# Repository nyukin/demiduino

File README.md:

Demiduino
=========

Hardware
--------

Demiduino is an open source
hardware circuit board designed to
introduce people to electronics
prototyping and the Arduino
platform.

The PCB design is inspired by an
Arduino, but divided in both
dimensions by 2.4. This makes it
smaller than an SD card and less
than 1 square inch in total.

There are only about a dozen
components, and they are all
through-hole mounted so that the
circuit can be assembled by
somebody who has had no previous
experience with soldering.

The microcontroller is a socketed
ATtiny85, so that replacing it or
leaving it in another circuit is
practical.

Power is provided by a USB mini
port or lithium battery cell with a
standard connector, and is
regulated by a 3 volt regulator.
This enables compatibiltiy with
many sensors and modules and low
power consumption.

Because the circuit focuses on low
BOM cost and part count to reach a
wider audience (read: I can give it
away to my friends without going
broke), there are some compromises
made that are a little dubious. A
proper engineer who went to college
has made a device that this one is
heavily based on, and it's called
the Trinket by Adafruit. It's
probably more reliable, but
features entirely SMD components.

Software
--------

The Trinket bootloader has been
recompiled from source with my own
USB VID/PID pair. This is to
appease the USB police and so I
must ask that you don't use my USB
pair for derivative work. I'll
happily detail how I accomplished
this and probably should write a
tutorial at least for my own
reference, because all this took me
a couple days to figure out.

To make the IDE work, I also have
recompiled avrdude 6, changing the
USBispTiny VID/PID pair to my own
as well. Then I drop the new
avrdude bin into ./Contents/Resources/Java/hardware/tools/avr/bin.
This is the same path for the
avrdude.conf file. Basically I
forked the Adafruit Trinket Arduino
IDE I had on my system and now it
won't work with a Trinket, so I
have more than one copy of the IDE
installed.

I also modified the boards.txt,
programmers.txt, and theme files.
The first two files were just to
cut out the uneccessary stuff, and
the theme file was to make a dark
colorscheme for the IDE that pays
homage to OSHPark's awesome purple
boards. Compiling avrdude was done
on Ubuntu... narwhal? I forget, but
I like narwhals so lets go with
that. And the IDE runs both on that
linux machine and on OS X 10.9.
Also the libraries I'm using in the
IDE need to be cleaned up to only
be what's compatible with
Demiduino.

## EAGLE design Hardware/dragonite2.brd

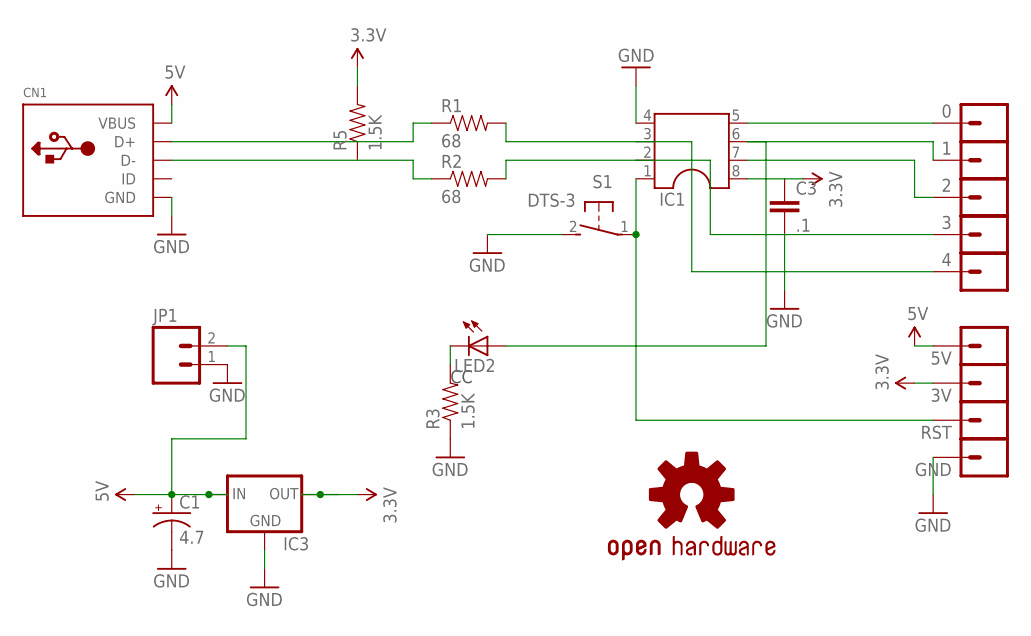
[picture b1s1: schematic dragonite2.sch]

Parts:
0, 1, 2, 3, 3V, 4, 5V: M01SMDNS; 1X01NS
C1: 4.7; E2-4
C3: .1; CAP-PTH-SMALLEZ
CN1: USBMOLEX; USB-MINIB-THM-MOLEX
GND: M01SMDNS; 1X01NS
IC1: DIL8; DIL08
IC3: V_REG_78XXTO-92; TO-92
JP1: M02JST-PTH-2; JST-2-PTH
LED2: LED3MM
R1, R2: 68; 1/6W-RES
R3, R5: 1.5K; 1/6W-RES
RST: M01SMDNS; 1X01NS
S1: DTS-3
U$4: OSHW-LOGOS; OSHW-LOGO-S

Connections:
3.3V: 3V.1, C3.1, IC1.8, IC3.3 (OUT), R5.2
5V: 5V.1, C1.+, CN1.VBUS, IC3.2 (IN), JP1.2
GND: C1.-, C3.2, CN1.GND, GND.1, IC1.4, IC3.1 (GND), JP1.1, R3.1, S1.2
unnamed: CN1.D+, R1.1
unnamed: CN1.D-, R2.1, R5.1
unnamed: LED2.K (C), R3.2
unnamed: IC1.1, RST.1, S1.1
unnamed: 4.1, IC1.3, R1.2
unnamed: 3.1, IC1.2, R2.2
unnamed: 0.1, IC1.5
unnamed: 1.1, IC1.6, LED2.A
unnamed: 2.1, IC1.7

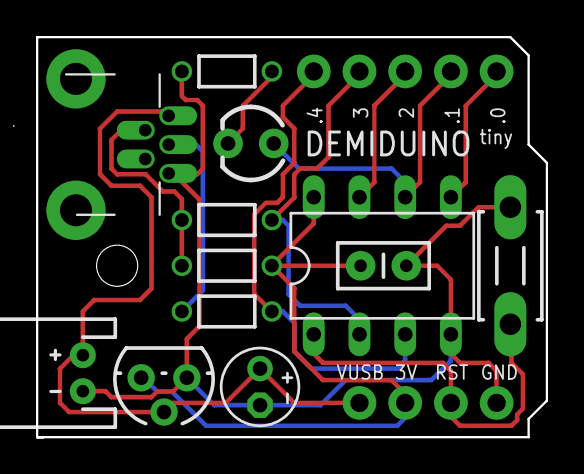
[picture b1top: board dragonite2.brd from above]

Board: 2 copper layers, 28.3 x 22.2 mm, 22 parts (1 on the bottom side), 12 nets.

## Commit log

2014-02-26 first commit
    first demiduino tiny stuff
2014-02-26 ide pic
    added a screenshot of what the ide looks like with my theme changes.
    the buttons are modified from the ones used in the solarized-based
    theme somebody else made, and they even included a .psd for them. find
    the forum post and give them credit.
2014-03-05 removed solder jumper
    removing the 5v solder jumper because it was pointless, moving the
    attiny, pin pads, and ceramic cap back .005 inches. centering the
    github silk on the back
2016-10-14 Removed a stray whitespace character.

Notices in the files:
parts and their libraries:
SparkFun: Licensing: CC v3.0 Share-Alike You are welcome to use this library for commercial purposes.
